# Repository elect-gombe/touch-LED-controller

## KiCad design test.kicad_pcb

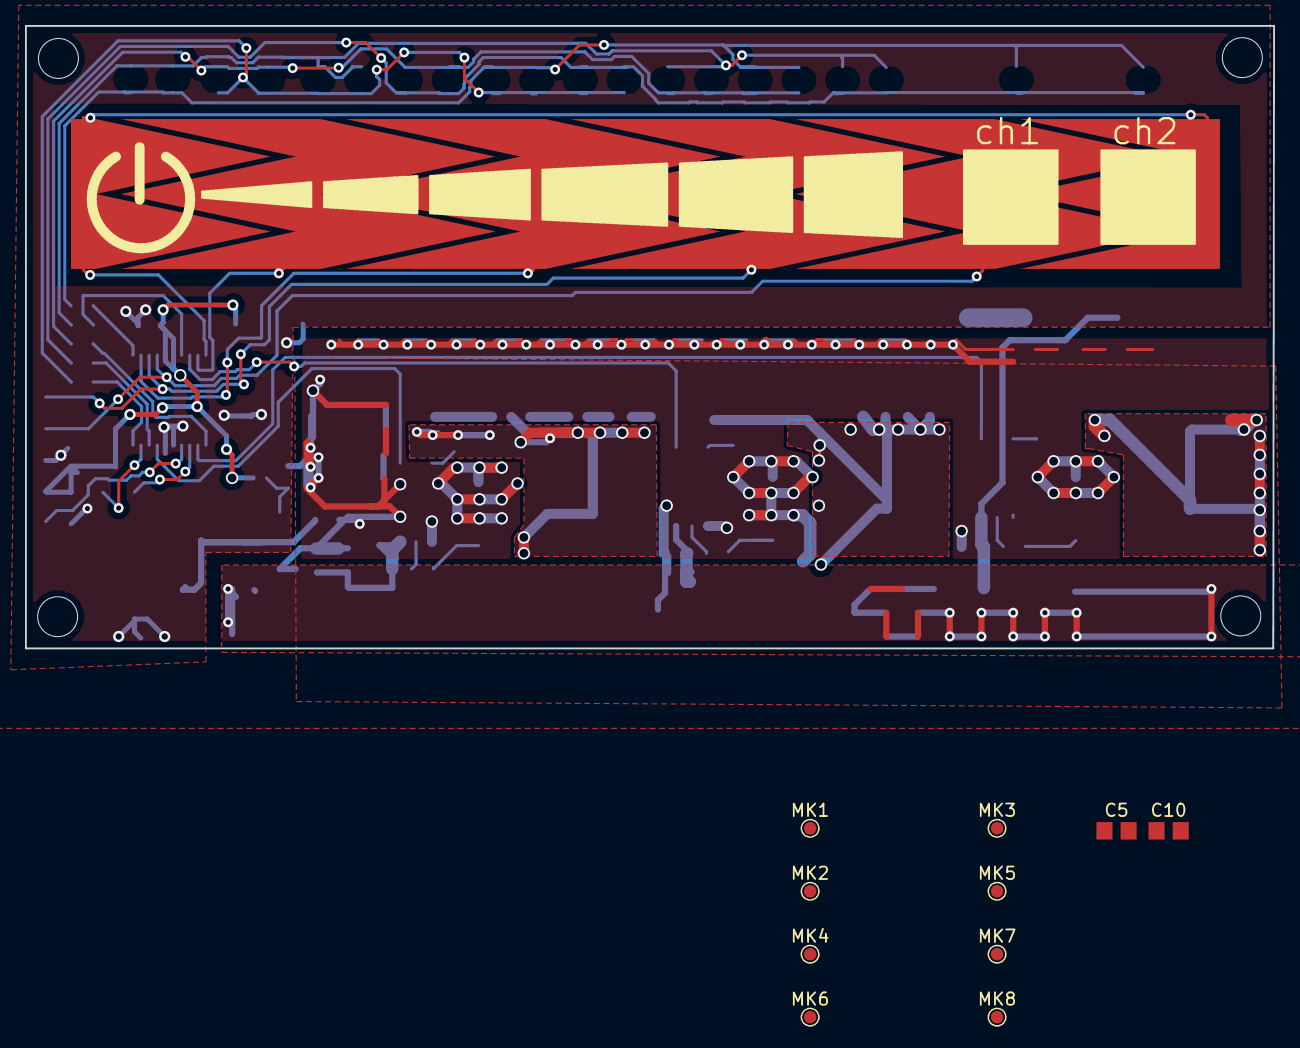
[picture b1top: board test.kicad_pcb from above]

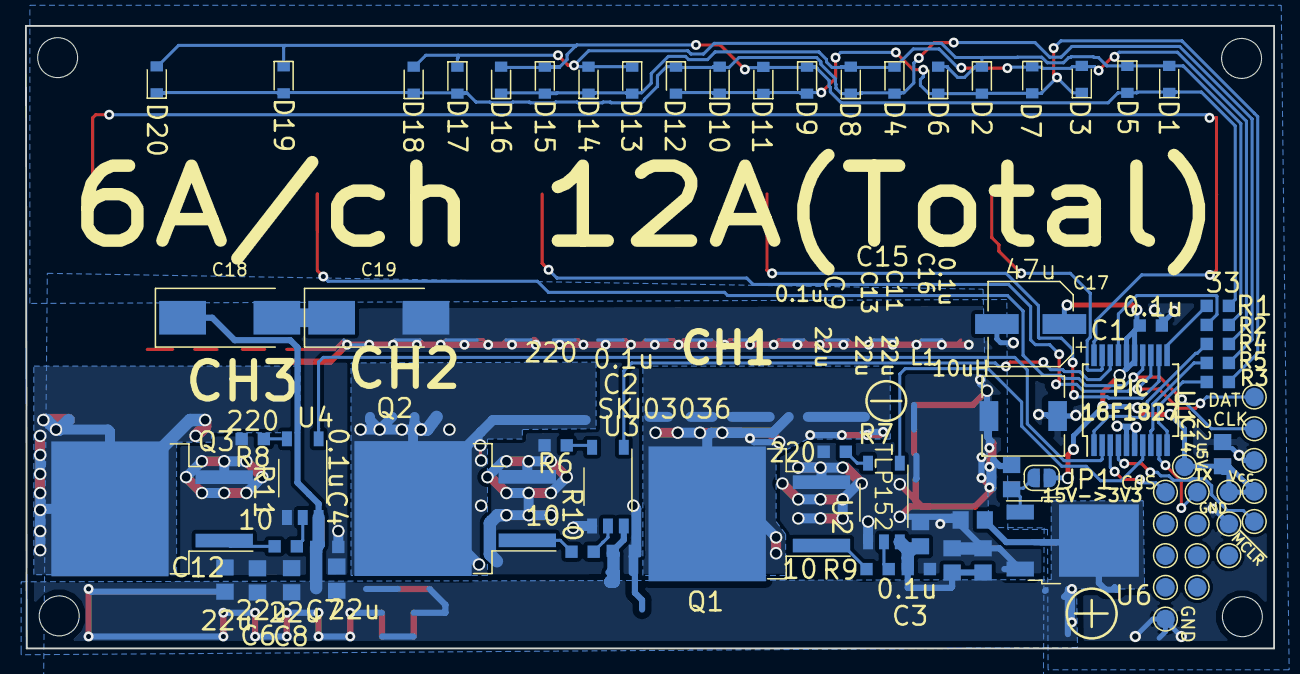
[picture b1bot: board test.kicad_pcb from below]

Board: 2 copper layers, 99.9 x 49.8 mm, 80 parts (69 on the bottom side), 39 nets.

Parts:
C1, C2, C3, C4: 0.1u; C_0603_1608Metric_Pad0.99x1.00mm_HandSolder
C5, C6, C7, C8, C9, C10, C11, C12, C13, C14: 22u; C_0805_2012Metric_Pad1.29x1.40mm_HandSolder
C15, C16: 0.1u; C_0805_2012Metric_Pad1.29x1.40mm_HandSolder
C17: 47u; CP_Elec_6.3x4.5
C18, C19: 100u 12.5V; CP_Tantalum_Case-X_EIA-7343-43_Hand
D1, D2, D3, D4, D5, D6, D7, D8, D9, D10, D11, D12, D13, D14, D15, D16, D17, D18, D19, D20: LED; LED_0603_1608Metric_Pad_ReverseMounted
JP1: Regulator; SolderJumper-2_P1.3mm_Open_RoundedPad1.0x1.5mm
L1: 10uH; L_6.3x6.3_H3
MK1, MK2, MK3, MK4, MK5, MK6, MK7, MK8: Mounting_Hole_PAD; TestPoint_Pad_D1.0mm
Q1, Q2, Q3: SKI03036; TO-263-2
R1, R2, R3, R4, R5: 33; R_0603_1608Metric_Pad0.99x1.00mm_HandSolder
R6, R7, R8: 220; R_0603_1608Metric_Pad0.99x1.00mm_HandSolder
R9, R10, R11: 10; R_0603_1608Metric_Pad0.99x1.00mm_HandSolder
TP1: ~MCLR; TestPoint_Pad_D1.5mm
TP2, TP2#3: Vcc; TestPoint_Pad_D1.5mm
TP2#2: 5V; TestPoint_Pad_D1.5mm
TP3, TP3#2, TP3#3: GND; TestPoint_Pad_D1.5mm
TP4: DAT; TestPoint_Pad_D1.5mm
TP5: CLK; TestPoint_Pad_D1.5mm
TP6: CdS; TestPoint_Pad_D1.5mm
TP7: DebugTx; TestPoint_Pad_D1.5mm
U1: PIC16F1933; SSOP-20_5.3x7.2mm_P0.65mm
U2, U3, U4: TLP152; MFSOP6-5_4.4x3.6mm_P1.27mm
U5: touchSlider5; mTouch3-1
U6: NJU7223; TO-252-2

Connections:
+5VD: C1.2, C14.2, C17.1, JP1.1, TP2.1, TP2#2.1, TP2#3.1, U1.15, U1.16
+12V: C2.1, C3.1, C4.1, C5.2, C6.1, C7.1, C8.1, C9.1, C10.1, C11.1, C12.1, C13.1, C15.1, C18.1, MK4.1, MK5.1, MK6.1, MK8.1, U2.6, U3.6, U4.6, U6.2
/CdS: TP6.1, U1.3
/DebugTx: TP7.1, U1.9
/ILED1: R1.2, U1.11
/ILED2: R2.2, U1.17
/ILED3: R3.2, U1.10
/ILED4: R4.2, U1.1
/ILED5: R5.2, U1.8
/IRsens: TP1.1, U1.4
/O1: MK1.1, Q1.2
/O2: MK2.1, Q2.2
/O3: MK3.1, Q3.2
/PWM1: U1.7, U2.1
/PWM2: U1.18, U3.1
/PWM3: U1.2, U4.1
GND: C2.2, C3.2, C4.2, C5.1, C6.2, C7.2, C8.2, C9.2, C10.2, C11.2, C12.2, C13.2, C15.2, C16.1, C19.2, L1.1, MK7.1, Q1.3, Q2.3, Q3.3, R6.2, R7.2, R8.2, U2.4, U3.4, U4.4, U6.3
GNDD: C1.1, C14.1, C17.2, L1.2, TP3.1, TP3#2.1, TP3#3.1, U1.5, U1.6
unnamed: C16.2, JP1.2, U6.1
unnamed: C18.2, C19.1
unnamed: D1.1, D5.2, D9.1, D11.2, D15.1, D16.2, D19.1, D20.2, R1.1
unnamed: D1.2, D2.1, D5.1, D6.2, D13.1, D14.2, D17.1, D18.2, R2.1
unnamed: D2.2, D3.1, D6.1, D7.2, D9.2, D10.1, D11.1, D12.2, R3.1
unnamed: D4.2, D8.1, D10.2, D12.1, D17.2, D18.1, D19.2, D20.1, R5.1
unnamed: D3.2, D4.1, D7.1, D8.2, D13.2, D14.1, D15.2, D16.1, R4.1
unnamed: Q1.1, R9.1
unnamed: Q2.1, R10.1
unnamed: Q3.1, R11.1
unnamed: R6.1, U3.3
unnamed: R7.1, U2.3
unnamed: R8.1, U4.3
unnamed: R9.2, U2.5
unnamed: R10.2, U3.5
unnamed: R11.2, U4.5
unnamed: TP4.1, U1.13, U5.4
unnamed: TP5.1, U1.14, U5.5
unnamed: U1.12, U5.3
unnamed: U1.19, U5.2
unnamed: U1.20, U5.1

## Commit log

2018-06-24 update 0625
    とりま基板完成？
